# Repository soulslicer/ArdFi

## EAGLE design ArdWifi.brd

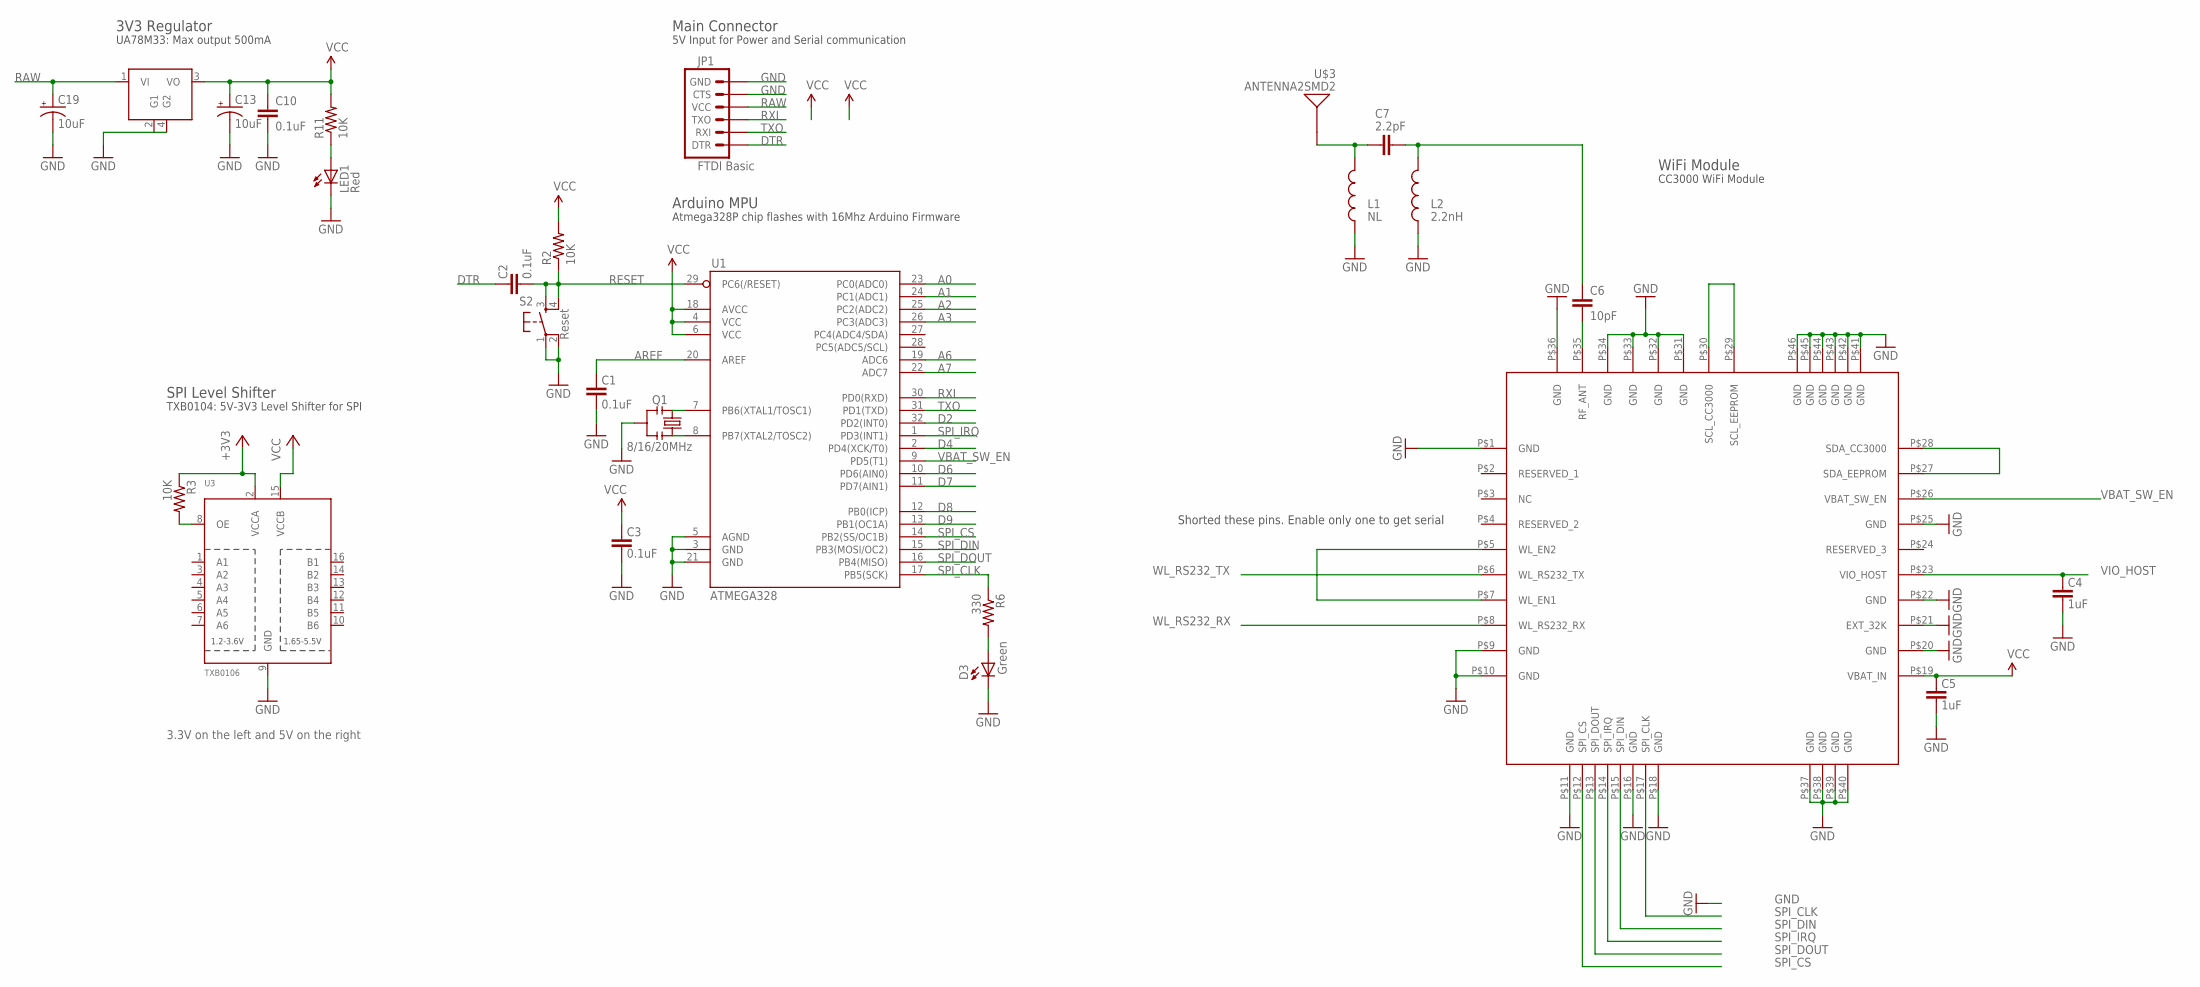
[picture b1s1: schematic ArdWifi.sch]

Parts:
C1, C2, C3, C10: 0.1uF; 0402-CAP
C4, C5: 1uF; 0402-CAP
C6: 10pF; 0402-CAP
C7: 2.2pF; 0402-CAP
C13, C19: 10uF; EIA3216
D3: Green; LED-0603
JP1: FTDI Basic; 1X06
L1: NL; C0402
L2: 2.2nH; C0402
LED1: Red; LED-0603
Q1: 8/16/20MHz; RESONATOR-SMD
R2, R11: 10K; 0402-RES
R3: 10K; R0603
R6: 330; 0402-RES
REG1: LDO_UA78M33; SOT223
S2: Reset; TACTILE_SWITCH_SMD
U1: ATMEGA328; TQFP32-08
U3: TXB0106; TSSOP16
U$1: CC3000
U$3: ANTENNA2SMD2; ANTENNA-CHIP3

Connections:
+3V3: R3.1, U3.2 (VCCA)
A0: U1.23 (PC0(ADC0))
A1: U1.24 (PC1(ADC1))
A2: U1.25 (PC2(ADC2))
A3: U1.26 (PC3(ADC3))
A6: U1.19 (ADC6)
A7: U1.22 (ADC7)
AREF: C1.2, U1.20 (AREF)
D2: U1.32 (PD2(INT0))
D4: U1.2 (PD4(XCK/T0))
D6: U1.10 (PD6(AIN0))
D7: U1.11 (PD7(AIN1))
D8: U1.12 (PB0(ICP))
D9: U1.13 (PB1(OC1A))
DTR: C2.2, JP1.1 (DTR)
GND: C1.1, C3.1, C4.1, C5.1, C10.2, C13.C (-), C19.C (-), D3.C, JP1.5 (CTS), JP1.6 (GND), L1.1, L2.1, LED1.C, Q1.2, REG1.2 (G1), REG1.4 (G2), S2.1, S2.2, U1.3 (GND), U1.5 (AGND), U1.21 (GND), U3.9 (GND), U$1.P$1 (GND), U$1.P$9 (GND), U$1.P$10 (GND), U$1.P$11 (GND), U$1.P$16 (GND), U$1.P$18 (GND), U$1.P$20 (GND), U$1.P$21 (EXT_32K), U$1.P$22 (GND), U$1.P$25 (GND), U$1.P$31 (GND), U$1.P$32 (GND), U$1.P$33 (GND), U$1.P$34 (GND), U$1.P$36 (GND), U$1.P$37 (GND), U$1.P$38 (GND), U$1.P$39 (GND), U$1.P$40 (GND), U$1.P$41 (GND), U$1.P$42 (GND), U$1.P$43 (GND), U$1.P$44 (GND), U$1.P$45 (GND), U$1.P$46 (GND)
unnamed: Q1.1, U1.8 (PB7(XTAL2/TOSC2))
unnamed: Q1.3, U1.7 (PB6(XTAL1/TOSC1))
unnamed: D3.A, R6.2
unnamed: C6.1, C7.2, L2.2
unnamed: C6.2, U$1.P$35 (RF_ANT)
unnamed: C7.1, L1.2, U$3.FEED
unnamed: U$1.P$29 (SCL_EEPROM), U$1.P$30 (SCL_CC3000)
unnamed: U$1.P$27 (SDA_EEPROM), U$1.P$28 (SDA_CC3000)
unnamed: LED1.A, R11.1
unnamed: R3.2, U3.8 (OE)
RAW: C19.A (+), JP1.4 (VCC), REG1.1 (VI)
RESET: C2.1, R2.1, S2.3, S2.4, U1.29 (PC6(/RESET))
RXI: JP1.3 (TXO), U1.30 (PD0(RXD))
SPI_CLK: R6.1, U1.17 (PB5(SCK)), U$1.P$17 (SPI_CLK)
SPI_CS: U1.14 (PB2(SS/OC1B)), U$1.P$12 (SPI_CS)
SPI_DIN: U1.15 (PB3(MOSI/OC2)), U$1.P$15 (SPI_DIN)
SPI_DOUT: U1.16 (PB4(MISO)), U$1.P$13 (SPI_DOUT)
SPI_IRQ: U1.1 (PD3(INT1)), U$1.P$14 (SPI_IRQ)
TXO: JP1.2 (RXI), U1.31 (PD1(TXD))
VBAT_SW_EN: U1.9 (PD5(T1)), U$1.P$26 (VBAT_SW_EN)
VCC: C3.2, C5.2, C10.1, C13.A (+), R2.2, R11.2, REG1.3 (VO), U1.4 (VCC), U1.6 (VCC), U1.18 (AVCC), U3.15 (VCCB), U$1.P$19 (VBAT_IN)
VIO_HOST: C4.2, U$1.P$23 (VIO_HOST)
WL_EN2: U$1.P$5 (WL_EN2), U$1.P$7 (WL_EN1)
WL_RS232_RX: U$1.P$8 (WL_RS232_RX)
WL_RS232_TX: U$1.P$6 (WL_RS232_TX)

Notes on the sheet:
Shorted these pins. Enable only one to get serial
3.3V on the left and 5V on the right
5V Input for Power and Serial communication
Main Connector
Atmega328P chip flashes with 16Mhz Arduino Firmware
Arduino MPU
UA78M33: Max output 500mA
3V3 Regulator
TXB0104: 5V-3V3 Level Shifter for SPI
SPI Level Shifter
WiFi Module
CC3000 WiFi Module

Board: 2 copper layers, 26 parts (1 on the bottom side), 27 nets, no tracks yet.

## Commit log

2013-12-17 Removed
2013-12-17 move stuff
2013-12-17 add wifi chip
2013-12-18 connect wifi chip
2013-12-19 added lvl shifter
